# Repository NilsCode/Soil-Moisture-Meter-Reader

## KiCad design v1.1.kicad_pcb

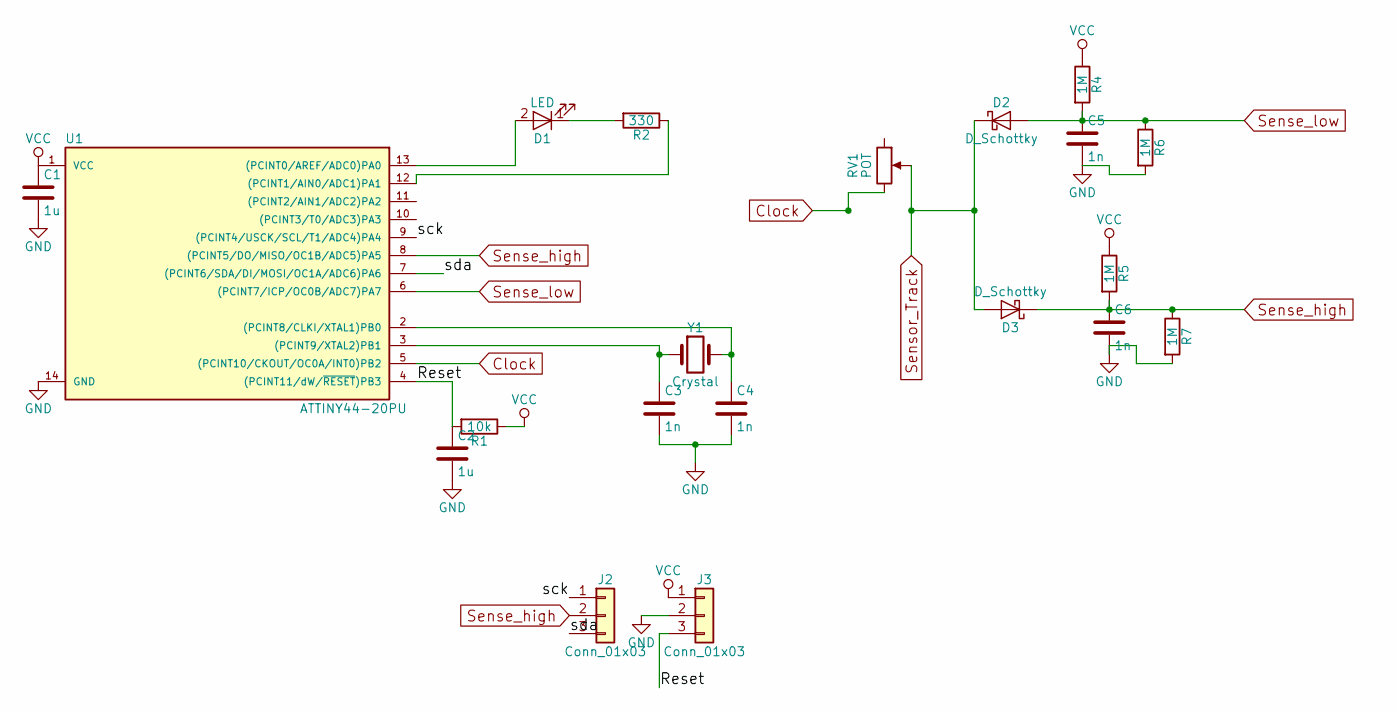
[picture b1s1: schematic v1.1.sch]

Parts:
C1, C2: 1u; C_Disc_D4.3mm_W1.9mm_P5.00mm
C3, C4, C5, C6: 1n; C_Disc_D4.3mm_W1.9mm_P5.00mm
D1: LED; LED_D3.0mm_FlatTop
D2, D3: D_Schottky; D_DO-41_SOD81_P7.62mm_Horizontal
J2, J3: Conn_01x03; Pin_Header_Straight_1x03_Pitch2.54mm
R1: 10k; R_Axial_DIN0204_L3.6mm_D1.6mm_P5.08mm_Horizontal
R2: 330; R_Axial_DIN0204_L3.6mm_D1.6mm_P5.08mm_Vertical
R4, R5, R6, R7: 1M; R_Axial_DIN0204_L3.6mm_D1.6mm_P5.08mm_Vertical
RV1: POT; Potentiometer_Trimmer_ACP_CA9h3.8_Vertical_Px3.8mm_Py5.0mm
U1: ATTINY44-20PU; DIP-14_W7.62mm
Y1: Crystal; Crystal_HC49-U_Vertical

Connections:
/Reset: C2.1, J3.3, R1.2, U1.4 ((PCINT11/dW/~RESET~)PB3)
/sck: J2.1, U1.9 ((PCINT4/USCK/SCL/T1/ADC4)PA4)
/sda: J2.3, U1.7 ((PCINT6/SDA/DI/MOSI/OC1A/ADC6)PA6)
Clock: RV1.3, U1.5 ((PCINT10/CKOUT/OC0A/INT0)PB2)
GND: C1.2, C2.2, C3.2, C4.2, C5.2, C6.2, J3.2, R6.2, R7.2, U1.14 (GND)
unnamed: C3.1, U1.3 ((PCINT9/XTAL2)PB1), Y1.1
unnamed: C4.1, U1.2 ((PCINT8/CLKI/XTAL1)PB0), Y1.2
unnamed: D1.1 (K), R2.2
unnamed: D1.2 (A), U1.13 ((PCINT0/AREF/ADC0)PA0)
unnamed: R2.1, U1.12 ((PCINT1/AIN0/ADC1)PA1)
Sense_high: C6.1, D3.1 (K), J2.2, R5.2, R7.1, U1.8 ((PCINT5/DO/MISO/OC1B/ADC5)PA5)
Sense_low: C5.1, D2.2 (A), R4.2, R6.1, U1.6 ((PCINT7/ICP/OC0B/ADC7)PA7)
Sensor_Track: D2.1 (K), D3.2 (A), RV1.2
VCC: C1.1, J3.1, R1.1, R4.1, R5.1, U1.1 (VCC)

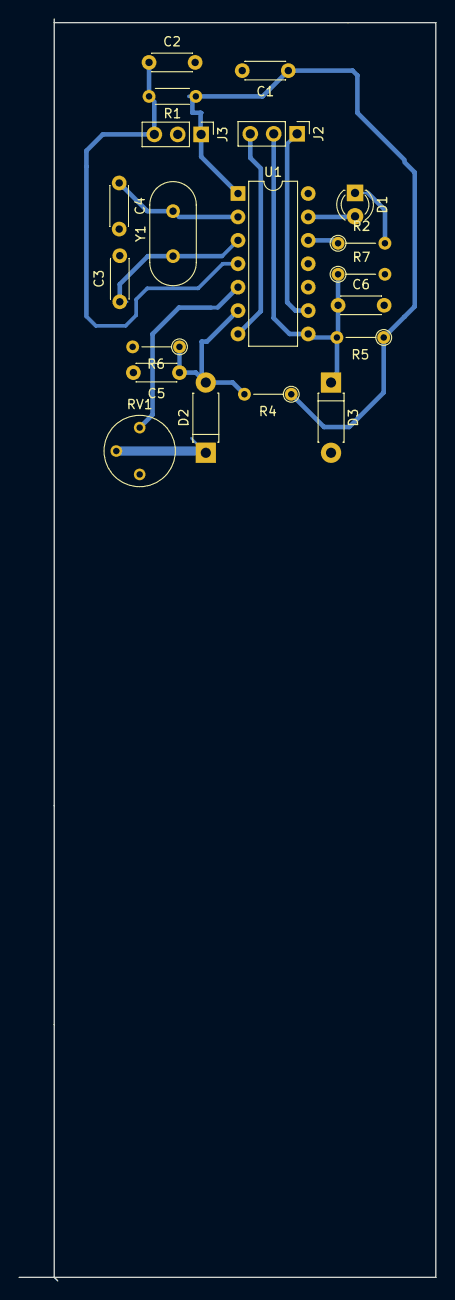
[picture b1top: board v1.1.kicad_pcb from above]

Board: 2 copper layers, 45.2 x 136.9 mm, 20 parts (0 on the bottom side), 14 nets.
